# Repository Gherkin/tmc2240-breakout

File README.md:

# TMC2240 Breakout
A small breakout board for the (formerly) Trinamatic [TMC2240 Stepper Motor Driver](https://www.analog.com/en/products/tmc2240.html)  

[Interactive BOM/PCB](https://gherkin.github.io/tmc2240-breakout/)  
[Interactive 3D Model](https://gherkin.github.io/tmc2240-breakout/3dmodel.html)  
[Schematic pdf](https://gherkin.github.io/tmc2240-breakout/tmc2240-breakout.pdf)

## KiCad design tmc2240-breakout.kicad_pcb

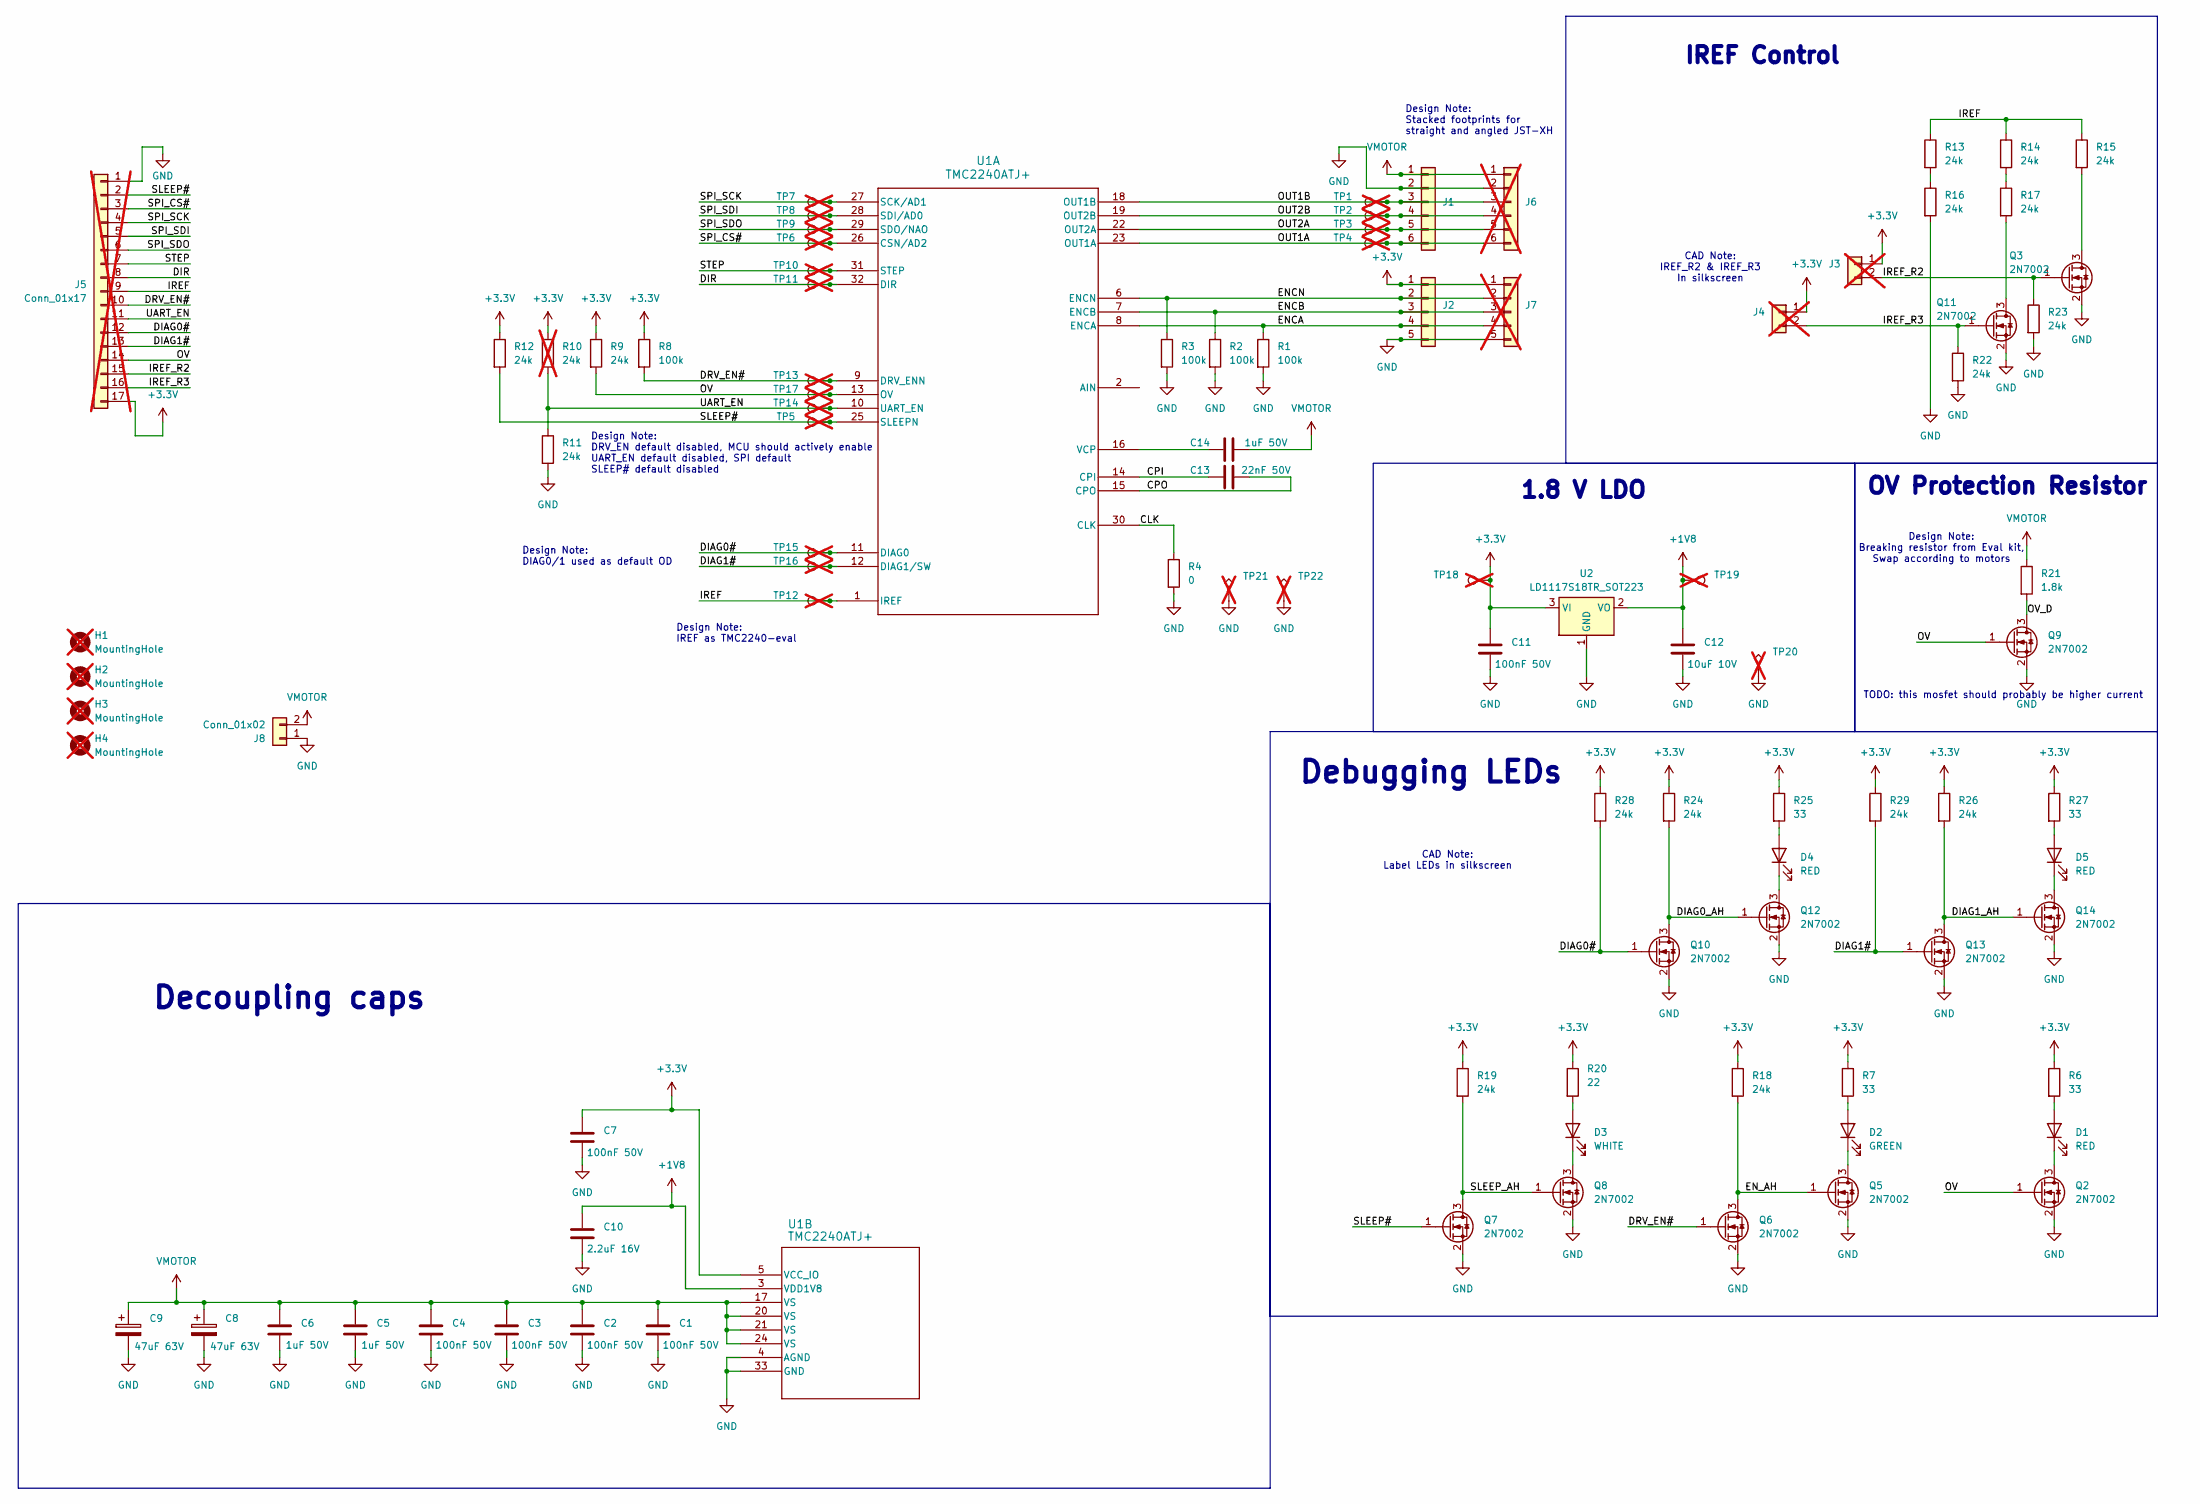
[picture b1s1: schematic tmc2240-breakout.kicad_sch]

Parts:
C1, C2, C3, C4, C7, C11: 100nF 50V; C_0402_1005Metric; LCSC C307331
C5, C6, C14: 1uF 50V; C_0603_1608Metric; LCSC C15849
C8, C9: 47uF 63V; CP_Elec_6.3x7.7; LCSC C72523
C10: 2.2uF 16V; C_0603_1608Metric; LCSC C23630
C12: 10uF 10V; C_0603_1608Metric; LCSC C19702
C13: 22nF 50V; C_0402_1005Metric; LCSC C1532
D1, D4, D5: RED; LED_0805_2012Metric; LCSC C84256
D2: GREEN; LED_0805_2012Metric; LCSC C2297
D3: WHITE; LED_0805_2012Metric; LCSC C34499
H1, H2, H3, H4: MountingHole; MountingHole_3.2mm_M3; not fitted
J1: Conn_01x06; CONN-TH_6P-P2.50_DEALON_XH-W-6A; LCSC C5160923
J2: Conn_01x05; CONN-TH_5P-P2.50_HDGC2501WR-5P; LCSC C5175258
J3, J4: Conn_01x02; PinHeader_1x02_P2.54mm_Vertical; LCSC C7429641; not fitted
J5: Conn_01x17; PinHeader_1x17_P2.54mm_Vertical; not fitted
J6: Conn_01x06; JST_XH_B6B-XH-A_1x06_P2.50mm_Vertical; LCSC C161873; not fitted
J7: Conn_01x05; JST_XH_B5B-XH-A_1x05_P2.50mm_Vertical; LCSC C125320; not fitted
J8: Conn_01x02; TerminalBlock_Phoenix_MKDS-1,5-2_1x02_P5.00mm_Horizontal
Q2, Q3, Q5, Q6, Q7, Q8, Q9, Q10, Q11, Q12, Q13, Q14: 2N7002; SOT-23; LCSC C8545
R1, R2, R3, R8: 100k; R_0402_1005Metric; LCSC C25530
R4: 0; R_0402_1005Metric; LCSC C60485
R6, R7, R25, R27: 33; R_0402_1005Metric; LCSC C25105
R9, R11, R12, R13, R14, R15, R16, R17, R18, R19, R22, R23, R24, R26, R28, R29: 24k; R_0201_0603Metric; LCSC C23352
R10: 24k; R_0201_0603Metric; LCSC C23352; not fitted
R20: 22; R_0402_1005Metric; LCSC C25092
R21: 1.8k; R_2512_6332Metric; LCSC C137011
TP1, TP2, TP3, TP4, TP5, TP6, TP7, TP8, TP9, TP10, TP11, TP12, TP13, TP14, TP15, TP16, TP17, TP18, TP19: TestPoint; TestPoint_THTPad_D1.0mm_Drill0.5mm; not fitted
TP20, TP21, TP22: TestPoint_Alt; TestPoint_THTPad_1.0x1.0mm_Drill0.5mm; not fitted
U1: TMC2240ATJ+; 21-0140_T3255+5C_TRI; LCSC C7429724
U2: LD1117S18TR_SOT223; SOT-223-3_TabPin2; LCSC C80598

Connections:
+1V8: C10.1, C12.1, TP19.1, U1.3 (VDD1V8), U2.2 (VO)
+3.3V: C7.1, C11.1, J2.1, J3.1, J4.1, J5.17, J7.1, R6.1, R7.1, R8.1, R9.1, R10.1, R12.1, R18.1, R19.1, R20.1, R24.1, R25.1, R26.1, R27.1, R28.1, R29.1, TP18.1, U1.5 (VCC_IO), U2.3 (VI)
/CLK: R4.1, U1.30 (CLK)
/CPI: C13.1, U1.14 (CPI)
/CPO: C13.2, U1.15 (CPO)
/DIAG0#: J5.12, Q10.1 (G), R28.2, TP15.1, U1.11 (DIAG0)
/DIAG0_AH: Q10.3 (D), Q12.1 (G), R24.2
/DIAG1#: J5.13, Q13.1 (G), R29.2, TP16.1, U1.12 (DIAG1/SW)
/DIAG1_AH: Q13.3 (D), Q14.1 (G), R26.2
/DIR: J5.8, TP11.1, U1.32 (DIR)
/DRV_EN#: J5.10, Q6.1 (G), R8.2, TP13.1, U1.9 (DRV_ENN)
/ENCA: J2.4, J7.4, R1.1, U1.8 (ENCA)
/ENCB: J2.3, J7.3, R2.1, U1.7 (ENCB)
/ENCN: J2.2, J7.2, R3.1, U1.6 (ENCN)
/EN_AH: Q5.1 (G), Q6.3 (D), R18.2
/IREF: J5.9, R13.1, R14.1, R15.1, TP12.1, U1.1 (IREF)
/IREF_R2: J3.2, J5.15, Q3.1 (G), R23.1
/IREF_R3: J4.2, J5.16, Q11.1 (G), R22.1
/OUT1A: J1.6, J6.6, TP4.1, U1.23 (OUT1A)
/OUT1B: J1.3, J6.3, TP1.1, U1.18 (OUT1B)
/OUT2A: J1.5, J6.5, TP3.1, U1.22 (OUT2A)
/OUT2B: J1.4, J6.4, TP2.1, U1.19 (OUT2B)
/OV: J5.14, Q2.1 (G), Q9.1 (G), R9.2, TP17.1, U1.13 (OV)
/OV_D: Q9.3 (D), R21.2
/SLEEP#: J5.2, Q7.1 (G), R12.2, TP5.1, U1.25 (SLEEPN)
/SLEEP_AH: Q7.3 (D), Q8.1 (G), R19.2
/SPI_CS#: J5.3, TP6.1, U1.26 (CSN/AD2)
/SPI_SCK: J5.4, TP7.1, U1.27 (SCK/AD1)
/SPI_SDI: J5.5, TP8.1, U1.28 (SDI/AD0)
/SPI_SDO: J5.6, TP9.1, U1.29 (SDO/NAO)
/STEP: J5.7, TP10.1, U1.31 (STEP)
/UART_EN: J5.11, R10.2, R11.1, TP14.1, U1.10 (UART_EN)
GND: C1.2, C2.2, C3.2, C4.2, C5.2, C6.2, C7.2, C8.2, C9.2, C10.2, C11.2, C12.2, J1.2, J2.5, J5.1, J6.2, J7.5, J8.1, Q2.2 (S), Q3.2 (S), Q5.2 (S), Q6.2 (S), Q7.2 (S), Q8.2 (S), Q9.2 (S), Q10.2 (S), Q11.2 (S), Q12.2 (S), Q13.2 (S), Q14.2 (S), R1.2, R2.2, R3.2, R4.2, R11.2, R16.2, R22.2, R23.2, TP20.1, TP21.1, TP22.1, U1.4 (AGND), U1.33 (GND), U2.1 (GND)
unnamed: D1.2 (A), R6.2
unnamed: D1.1 (K), Q2.3 (D)
unnamed: D2.2 (A), R7.2
unnamed: D2.1 (K), Q5.3 (D)
unnamed: D3.2 (A), R20.2
unnamed: D3.1 (K), Q8.3 (D)
unnamed: D4.2 (A), R25.2
unnamed: D4.1 (K), Q12.3 (D)
unnamed: D5.2 (A), R27.2
unnamed: D5.1 (K), Q14.3 (D)
unnamed: Q3.3 (D), R15.2
unnamed: Q11.3 (D), R17.2
unnamed: R13.2, R16.1
unnamed: R14.2, R17.1
unnamed: C14.1, U1.16 (VCP)
VMOTOR: C1.1, C2.1, C3.1, C4.1, C5.1, C6.1, C8.1, C9.1, C14.2, J1.1, J6.1, J8.2, R21.1, U1.17 (VS), U1.20 (VS), U1.21 (VS), U1.24 (VS)

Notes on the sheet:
IREF Control
Design Note: DRV_EN default disabled, MCU should actively enable UART_EN default disabled, SPI default SLEEP# default disabled
TODO: this mosfet should probably be higher current
Design Note: DIAG0/1 used as default OD
1.8 V LDO
Debugging LEDs
Design Note: Breaking resistor from Eval kit, Swap according to motors
CAD Note: Label LEDs in silkscreen
OV Protection Resistor
Design Note: IREF as TMC2240-eval
Design Note: Stacked footprints for straight and angled JST-XH
Decoupling caps
CAD Note: IREF_R2 & IREF_R3 In silkscreen

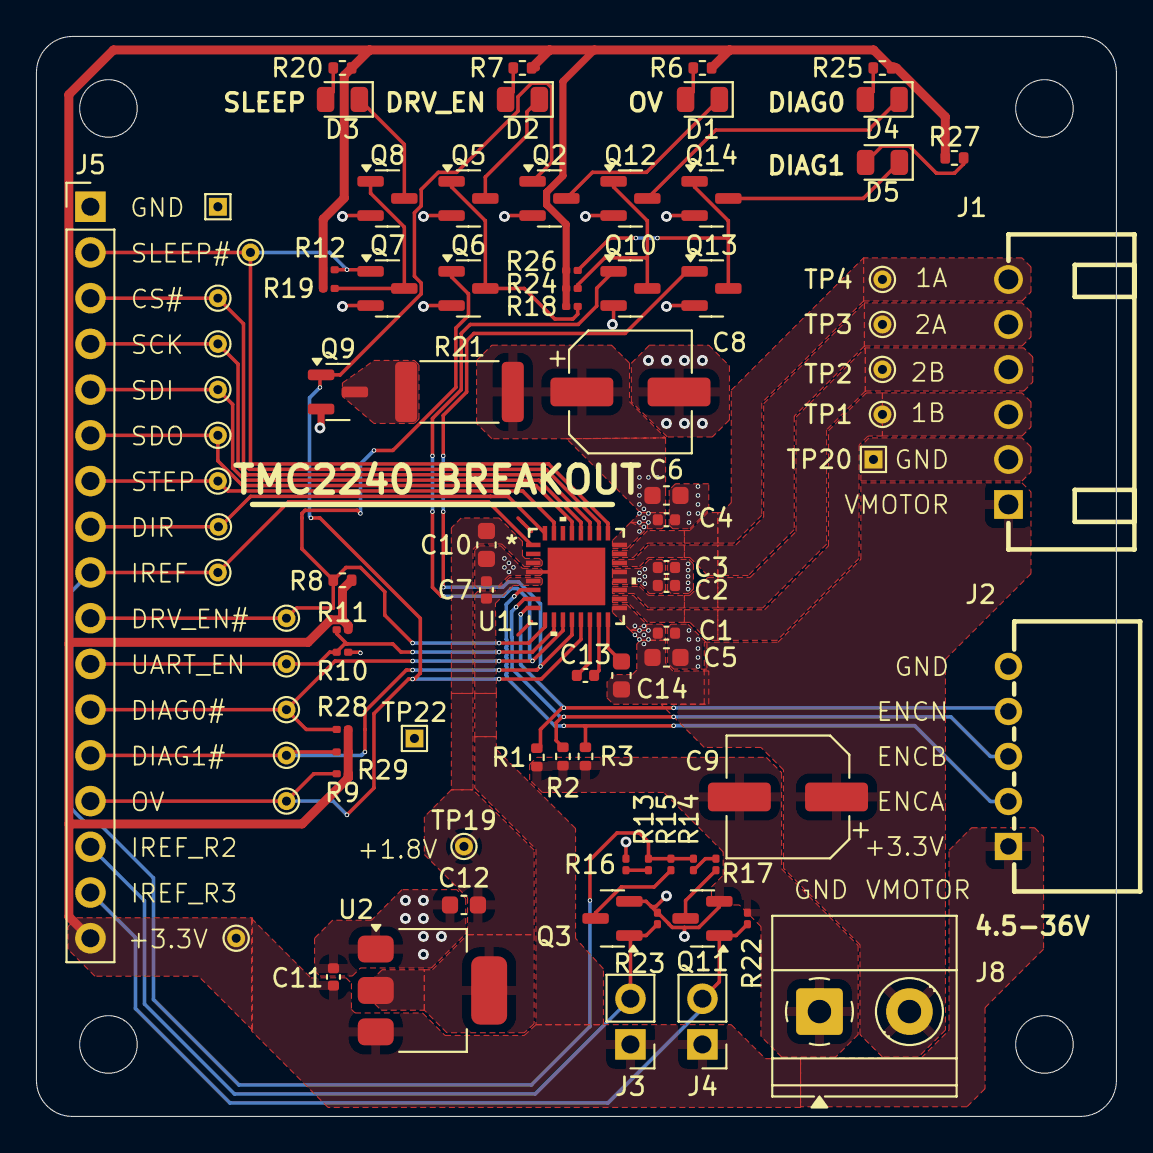
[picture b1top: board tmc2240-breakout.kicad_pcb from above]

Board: 2 copper layers, 60.0 x 60.0 mm, 93 parts (1 on the bottom side), 48 nets.

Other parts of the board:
QR*****: tmc2240-breakout; //github.com/Gherkin/tmc2240-breakout

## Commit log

2025-03-27 init
2025-03-27 did some stuff
2025-03-29 renamed kicad files correctly
2025-03-29 added git hooks
2025-03-30 did more stuff
2025-04-01 did some minor things, organized schematic a bit
2025-04-02 did a lot of sourcing of lcsc, most is basic
2025-04-06 did more sourcing and footprints
2025-04-08 did more sourcing and fixed footprints
2025-04-08 did some pcb placement
2025-04-08 did some more placements
2025-04-09 started doing some routing
2025-04-09 trying to export 3d model
2025-04-09 added 3d model
2025-04-09 trying to add 3d model viewer
2025-04-09 changed 3dmodel viewer
2025-04-09 fixed error in 3dmodel html
2025-04-09 more changed to 3d model
2025-04-09 even more changed to 3d model
2025-04-10 did some more pcb layout
2025-04-11 did some layouting
2025-04-18 old commit
2025-04-18 more layouting
2025-04-19 more pcb layout
2025-04-19 did some more layouting
2025-04-21 more pcb layouting
2025-04-21 updated 3d model
2025-04-21 pretty much done with layout, review time
